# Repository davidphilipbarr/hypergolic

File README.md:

# hypergolic

Ergo 34 keyboard(s) that uses no diodes. 

## HERE BE DRAGONS

Some files maybe named wrong, eg left and right may be incorrect, you will need to check which way around they are by tracing the RAW line or some other method you cooked up yourself.

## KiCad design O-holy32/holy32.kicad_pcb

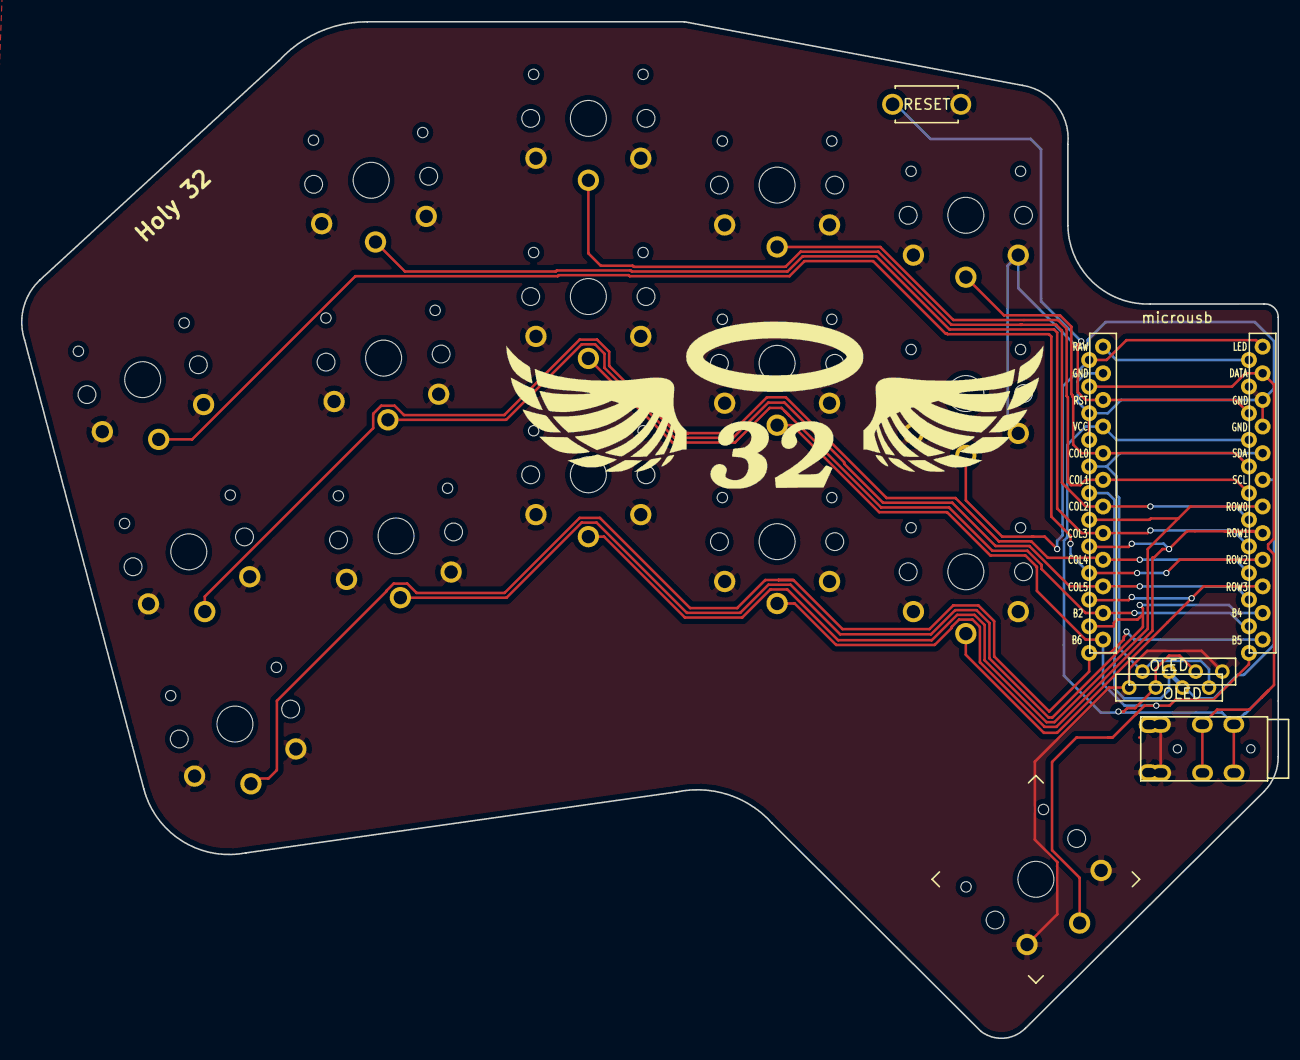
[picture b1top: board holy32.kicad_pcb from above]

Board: 2 copper layers, 119.8 x 96.9 mm, 21 parts (0 on the bottom side), 21 nets.

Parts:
Jack0: TRRS; TRRS-PJ-DPB2
OLED1, OLED1#2: Conn_01x04; OLED_1side
RSW1: SW_Push; ResetSW
SW2, SW3, SW4, SW5, SW6, SW8, SW9, SW10, SW11, SW12, SW14, SW15, SW16, SW17, SW18: SW_Push; SW_PG1350_rev_DPB
SW20: SW_Push; SW_PG1350_15_reversible_b2
U1: ProMicro-kbd; ProMicro_v2

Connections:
Switch1: SW2.1, U1.9
Switch2: SW3.1, U1.17
Switch3: SW4.1, U1.18
Switch4: SW5.1, U1.19
Switch5: SW6.1, U1.20
Switch6: SW8.1, U1.16
Switch7: SW9.1, U1.15
Switch8: SW10.1, U1.14
Switch9: SW11.1, SW20.1, U1.13
Switch10: SW12.1, U1.1
Switch11: OLED1.4, OLED1#2.4, U1.5
Switch12: OLED1.3, OLED1#2.3, U1.6
Switch13: SW16.1, U1.7
Switch14: SW17.1, U1.8
Switch15: SW18.1, U1.10
Switch16: SW15.1, U1.11
Switch17: SW14.1, U1.12
Switch18: Jack0.R1, U1.2
gnd: Jack0.S, Jack0.T, OLED1.1, OLED1#2.1, RSW1.1, SW2.2, SW3.2, SW4.2, SW5.2, SW6.2, SW8.2, SW9.2, SW10.2, SW11.2, SW12.2, SW14.2, SW15.2, SW16.2, SW17.2, SW18.2, SW20.2, U1.3, U1.4, U1.23
reset: RSW1.2, U1.22
vcc: Jack0.R2, OLED1.2, OLED1#2.2, U1.21

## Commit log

2021-06-23 ground control
2021-06-24 more ground, fuck.
2021-06-29 thumb becomes embiggened
2021-06-29 gerbers for shoggs
2021-07-12 flip left power switch and add plate file
2021-08-06 more grounding
2021-08-15 Experimental trrs version
2021-08-15 add snap
2021-08-15 fill
2021-08-15 move apart a bit
2021-09-10 move trrs things, make effort at actual symmetry
2021-09-10 hypergolic with a pinky cluster.
2021-09-29 update most of hypergarlic and add a half
2021-11-08 softer
2021-11-24 add image
2021-11-24 32 keys
2022-08-10 move paroxysm to own repo
2022-12-20 almost a year old, but here we are
2023-05-08 dubious gerbers, chance your arm?
